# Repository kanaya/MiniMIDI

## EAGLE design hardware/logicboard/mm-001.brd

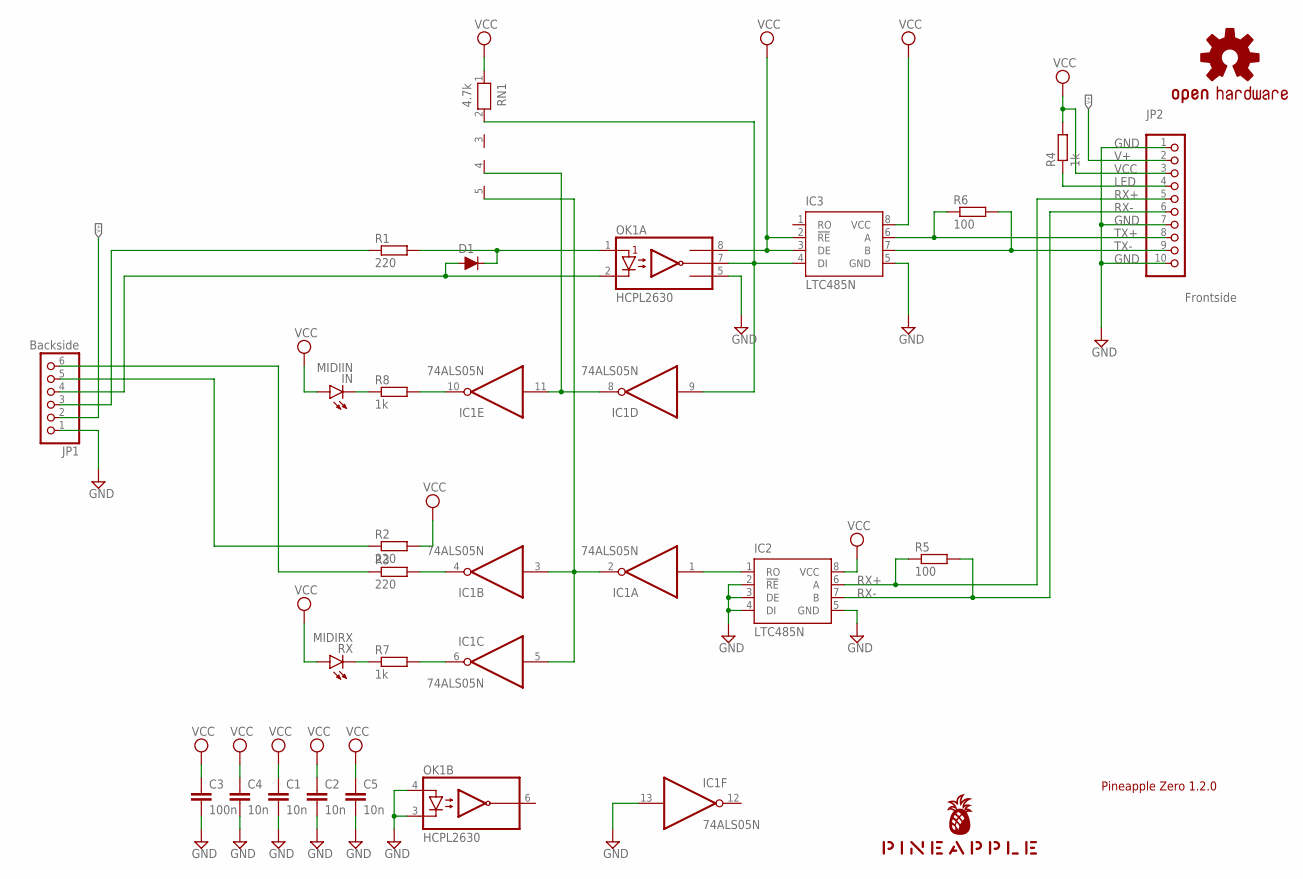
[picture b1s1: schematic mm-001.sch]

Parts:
C1, C2, C4, C5: 10n; C025-024X044
C3: 100n; C025-024X044
D1: DIODE-1N4148
IC1: 74ALS05N; DIL14
IC2, IC3: LTC485N; DIL08
IN: MIDIIN; LED3MM
JP1: Backside; 1X06
JP2: Frontside; 1X10
LOGO1: OSHW-LOGOS-COPPER; OSHW-LOGO-S_COPPER
OK1: HCPL2630; DIL08
R1, R2, R3: 220; 0204/5
R4, R7, R8: 1k; 0204/5
R5, R6: 100; 0204/5
RN1: 4.7k; RN-5
RX: MIDIRX; LED3MM
U$1: PINEAPPLE450

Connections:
LED: JP2.4, R4.1
LED1: IC1.6 (O), R7.2
LED1K: R7.1, RX.K (C)
LED2: IC1.10 (O), R8.2
LED2K: IN.K (C), R8.1
MIDIIN: D1.C, OK1.1 (A1), R1.2
MIRTN: D1.A, JP1.4, OK1.2 (C1)
MISND: JP1.3, R1.1
MOSND: JP1.5, R2.1
unnamed: IC1.1 (I), IC2.1 (RO)
unnamed: IC1.4 (O), R3.2
unnamed: IC1.8 (O), IC1.11 (I), RN1.4
NMIDIOUT: IC1.2 (O), IC1.3 (I), IC1.5 (I), RN1.5
RX+: IC2.6 (A), JP2.5, R5.1
RX-: IC2.7 (B), JP2.6, R5.2
TX: IC1.9 (I), IC3.4 (DI), OK1.7 (VO1), RN1.2
TX+: IC3.6 (A), JP2.8, R6.1
TX-: IC3.7 (B), JP2.9, R6.2
V+: JP1.2, JP2.2
VCC: C1.1, C2.1, C3.1, C4.1, C5.1, IC1.14 (VCC), IC2.8 (VCC), IC3.2 (!RE), IC3.3 (DE), IC3.8 (VCC), IN.A, JP2.3, OK1.8 (VCC), R2.2, R4.2, RN1.1, RX.A

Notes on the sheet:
Pineapple Zero 1.2.0

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
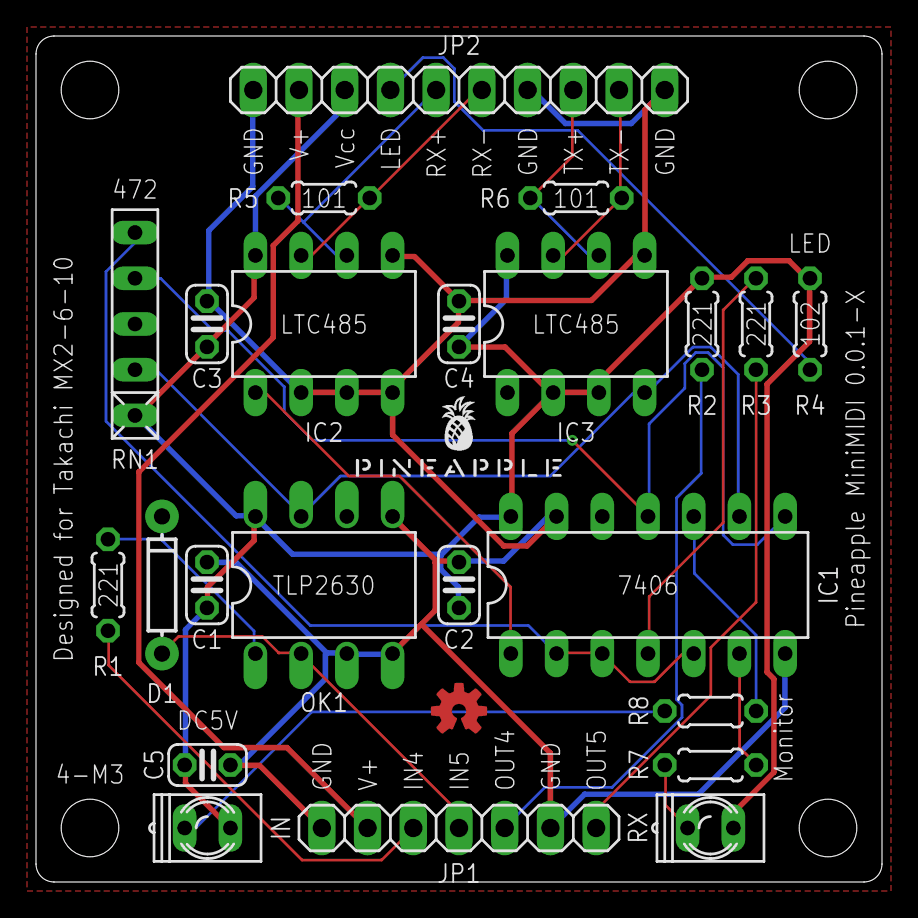
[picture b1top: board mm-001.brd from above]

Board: 2 copper layers, 47.0 x 47.0 mm, 25 parts (0 on the bottom side), 22 nets.

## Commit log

2022-11-11 Imported from Pineapple Zero.
2022-11-11 Trying to fit in to the new platform.
2022-11-11 First try.
2022-11-12 Artwork.
2022-11-12 Mostly done.
2022-11-12 Panel design.
2022-11-12 Silk.
2022-11-12 Rebuild.
2022-11-13 Finish up.
2022-11-13 New panel design.
2022-11-14 Swapped DC and MIDIs of the panel.
2022-11-14 Added outline to the panel design.
2022-11-16 Added test leds.
2022-11-19 TX+/TX-/GND, RX+/RX-/GND.
2022-11-20 Changed positions of the monitor leds.
2022-11-20 Changed panel design.

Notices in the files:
parts and their libraries:
SparkFun-Aesthetics: Licensing: Creative Commons ShareAlike 4.0 International - https://creativecommons.org/licenses/by-sa/4.0
